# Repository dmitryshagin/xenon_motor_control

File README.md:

# xenon_motor_control
Board to control xenon headlight position with conventional halogen control for VW Passat B5+ car.
Bolt-con connectors that fit: Pigtail 968813-9C 0-1452576-8
https://aliexpress.ru/item/4000353686621.html?spm=a2g0s.9042311.0.0.ddc433edCFKElc

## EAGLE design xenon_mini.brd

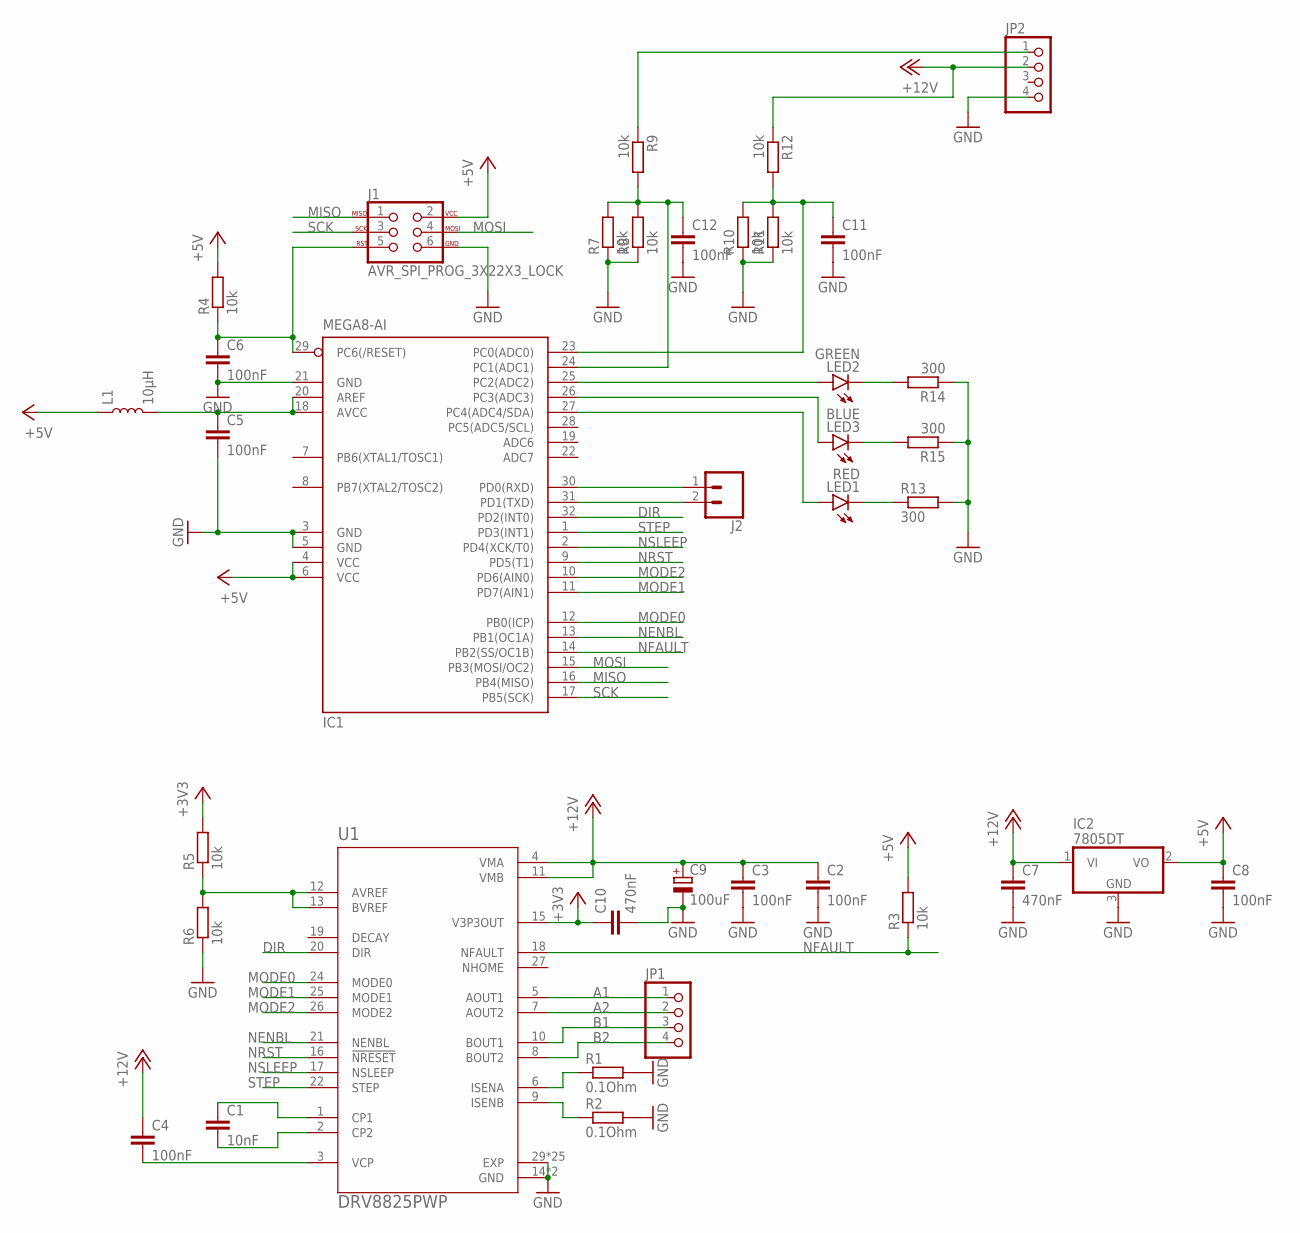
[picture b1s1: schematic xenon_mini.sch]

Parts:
C1: 10nF; C0603; LCSC C57112
C2, C3, C4, C8: 100nF; C0603; LCSC C14663
C5, C6, C11, C12: 100nF; C0603; LCSC CC0603KRX7R9BB104
C7, C10: 470nF; C0603; LCSC C1623
C9: 100uF; UD-6,3X7,7_NICHICON; LCSC C176675
IC1: MEGA8-AI; TQFP32-08; LCSC C8727
IC2: 7805DT; TO252; LCSC C310413
J1: AVR_SPI_PROG_3X22X3_LOCK; 2X3_LOCK
J2: CONN_02LOCK; 1X02_LOCK
JP1, JP2: PINHD-1X4; 1X04
L1: 10μH; 0805; LCSC C1046
LED1: RED; SML0603; LCSC C2286
LED2: GREEN; SML0603; LCSC C72043
LED3: BLUE; SML0603; LCSC C72041
R1, R2: 0.1Ohm; R1206; LCSC C25334
R3, R4, R5, R6, R7, R8, R9, R10, R11, R12: 10k; R0603; LCSC C25804
R13, R14, R15: 300; R0603; LCSC C23025
U1: DRV8825PWP; SOP65P640X120-29N; LCSC C81582

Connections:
+3V3: C10.1, R5.2, U1.15 (V3P3OUT)
+5V: C8.1, IC1.4 (VCC), IC1.6 (VCC), IC2.2 (VO), J1.2, L1.1, R3.2, R4.2
+12V: C2.1, C3.1, C4.1, C7.1, C9.+, IC2.1 (VI), JP2.2, R12.1, U1.4 (VMA), U1.11 (VMB)
A1: JP1.1, U1.5 (AOUT1)
A2: JP1.2, U1.7 (AOUT2)
B1: JP1.3, U1.10 (BOUT1)
B2: JP1.4, U1.8 (BOUT2)
DIR: IC1.32 (PD2(INT0)), U1.20 (DIR)
GND: C2.2, C3.2, C5.2, C6.2, C7.2, C8.2, C9.-, C10.2, C11.2, C12.2, IC1.3 (GND), IC1.5 (GND), IC1.21 (GND), IC2.3 (GND), J1.6, JP2.4, R1.2, R2.2, R6.1, R7.1, R8.1, R10.1, R11.1, R13.2, R14.1, R15.1, U1.14 (GND), U1.28 (GND), U1.29 (EXP), U1.P1 (EXP), U1.P2 (EXP), U1.P3 (EXP), U1.P4 (EXP), U1.P5 (EXP), U1.P6 (EXP), U1.P7 (EXP), U1.P8 (EXP), U1.P9 (EXP), U1.P10 (EXP), U1.P11 (EXP), U1.P12 (EXP), U1.P13 (EXP), U1.P14 (EXP), U1.P15 (EXP), U1.P16 (EXP), U1.P17 (EXP), U1.P18 (EXP), U1.P19 (EXP), U1.P20 (EXP), U1.P21 (EXP), U1.P22 (EXP), U1.P23 (EXP), U1.P24 (EXP)
MISO: IC1.16 (PB4(MISO)), J1.1
MODE0: IC1.12 (PB0(ICP)), U1.24 (MODE0)
MODE1: IC1.11 (PD7(AIN1)), U1.25 (MODE1)
MODE2: IC1.10 (PD6(AIN0)), U1.26 (MODE2)
MOSI: IC1.15 (PB3(MOSI/OC2)), J1.4
unnamed: C1.1, U1.1 (CP1)
unnamed: C1.2, U1.2 (CP2)
unnamed: C4.2, U1.3 (VCP)
unnamed: R1.1, U1.6 (ISENA)
unnamed: R2.1, U1.9 (ISENB)
unnamed: C6.1, IC1.29 (PC6(/RESET)), J1.5, R4.1
unnamed: C12.1, IC1.24 (PC1(ADC1)), R7.2, R8.2, R9.2
unnamed: C11.1, IC1.23 (PC0(ADC0)), R10.2, R11.2, R12.2
unnamed: LED1.C, R13.1
unnamed: JP2.1, R9.1
unnamed: R5.1, R6.2, U1.12 (AVREF), U1.13 (BVREF)
unnamed: IC1.30 (PD0(RXD)), J2.1
unnamed: IC1.31 (PD1(TXD)), J2.2
unnamed: IC1.25 (PC2(ADC2)), LED2.A
unnamed: IC1.26 (PC3(ADC3)), LED3.A
unnamed: LED2.C, R14.2
unnamed: LED3.C, R15.2
unnamed: IC1.27 (PC4(ADC4/SDA)), LED1.A
unnamed: C5.1, IC1.18 (AVCC), IC1.20 (AREF), L1.2
NENBL: IC1.13 (PB1(OC1A)), U1.21 (NENBL)
NFAULT: IC1.14 (PB2(SS/OC1B)), R3.1, U1.18 (NFAULT)
NRST: IC1.9 (PD5(T1)), U1.16 (!NRESET)
NSLEEP: IC1.2 (PD4(XCK/T0)), U1.17 (NSLEEP)
SCK: IC1.17 (PB5(SCK)), J1.3
STEP: IC1.1 (PD3(INT1)), U1.22 (STEP)

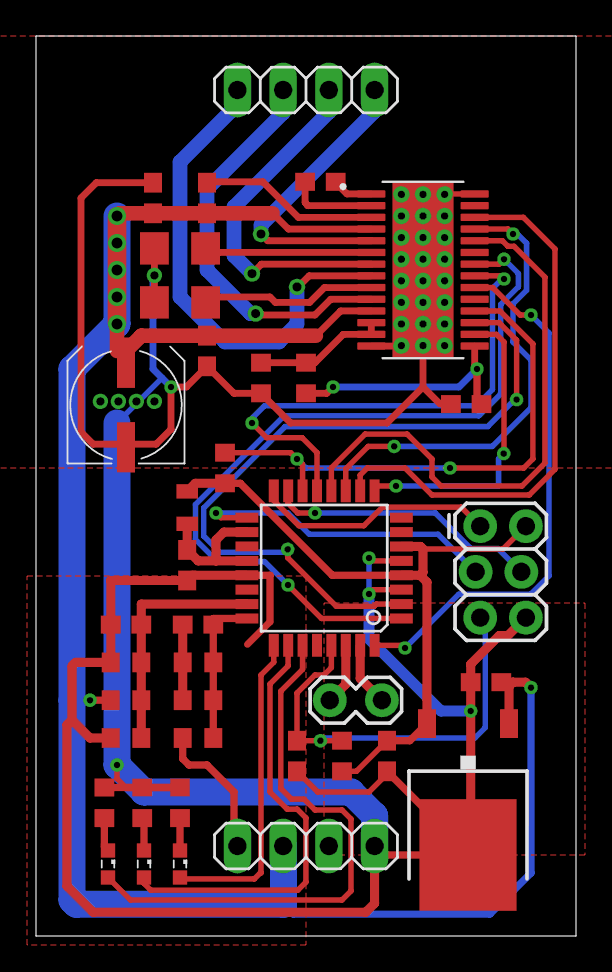
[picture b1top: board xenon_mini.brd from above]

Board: 2 copper layers, 30.0 x 50.0 mm, 38 parts (0 on the bottom side), 39 nets.

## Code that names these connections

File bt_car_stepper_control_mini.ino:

//+PC0 - voltage in
//+PC1 - corrector in

//+PC2 - green LED
//+PC3 - blue LED
//+PC4 - RED LED

//+PD2 - DIR 
//+PD3 - STEP
//+PD4 - NSLEEP
//+PD5 - NRST
//+PD6 - MODE1
//+PD7 - MODE2

//+PB0 - MODE0
//+PB1 - NENBL
//+PB2 - NFAULT
#define READS_TO_AVERAGE 50

const int dirPin = 2;
const int stepPin = 3;
const int sleepPin = 4;
const int resetPin = 5;
const int ms1Pin = 8;
const int ms2Pin = 7;
const int ms3Pin = 6;
const int enablePin = 9;
const int faultPin = 10;


const int voltageInPin = A0;
const int correctorInPin = A1;
const int greenLED = A2;
const int blueLED = A3;
const int redLED = A4;
const int step_delay = 600; //1000 is minimum for a full step
const int steps_total = 360; //its 360 full steps

int currentPosition = steps_total; //let's assume we are all way up un the start
uint32_t motor_last_moved_at = 0;

int previous_direction = 0;
uint8_t driver_enabled = 0;

uint32_t voltageIn = 0;
uint32_t correctorIn = 0;

uint32_t newVoltageIn = 0;
uint32_t newCorrectorIn = 0;
uint16_t reads_made = 0;
uint16_t reads_reference_made = 0;

int minVal = 0;
int maxVal = 1023;
int target = 0;

//for left headlight: GREEN - corrector input (pin 6), BLACK - +12 (pin2), RED - GND (pin 4)

// vin   = 13.4V
// corr0 = 11.1V . =>80% of vin => max
// corr1 = 9.7V
// corr2 = 7.7V
// corr3 = 5.4V <= 40% of vin => min.

void disable(){
//  digitalWrite(sleepPin, LOW);
  digitalWrite(enablePin, HIGH);
  digitalWrite(blueLED, LOW);
  driver_enabled = 0;
}

void enable(){
  if(driver_enabled){
    return;
  }
  digitalWrite(blueLED, HIGH);
  digitalWrite(enablePin, LOW);
//  delayMicroseconds(2000);
  delay(3);//it requires at least 1.7ms to start accepting data.
  driver_enabled = 1;
}

void moveToPosition(int target) {
  enable(); //power up driver
  int steps_count = 0;
  if(target < currentPosition) {
    digitalWrite(dirPin, LOW); // retract
    steps_count = currentPosition - target;
    previous_direction = 1;
  } else {
    digitalWrite(dirPin, HIGH); // extend
    steps_count = target - currentPosition;
    previous_direction = 0;
  }
  for (int x = 0; x < steps_count * 2; x++) { //x2 due to microstepping
    digitalWrite(stepPin, HIGH);
    delayMicroseconds(step_delay);
    digitalWrite(stepPin, LOW);
    delayMicroseconds(step_delay);
  }
  currentPosition = target;
//  disable(); // Release motor to avoid overheating
}

void setup() {
  delayMicroseconds(10000);
  pinMode(redLED, OUTPUT);
  digitalWrite(redLED, LOW);
  pinMode(greenLED, OUTPUT);
  digitalWrite(greenLED, HIGH);
  pinMode(blueLED, OUTPUT);
  digitalWrite(blueLED, LOW);
  pinMode(stepPin, OUTPUT);
  pinMode(dirPin, OUTPUT);
  
  pinMode(ms1Pin, OUTPUT);
  pinMode(ms2Pin, OUTPUT);
  pinMode(ms3Pin, OUTPUT);
  pinMode(resetPin, OUTPUT);
  pinMode(enablePin, OUTPUT);
  pinMode(sleepPin, OUTPUT);

  pinMode(faultPin, INPUT);

  pinMode(correctorInPin, INPUT);
  pinMode(voltageInPin, INPUT);

  digitalWrite(ms1Pin, HIGH);
  digitalWrite(ms2Pin, LOW);
  digitalWrite(ms3Pin, LOW); // Step to 1/2 step
  digitalWrite(resetPin, HIGH);
  digitalWrite(sleepPin, HIGH);
  disable();
  digitalWrite(blueLED, LOW);

  analogReference(EXTERNAL);
  
  Serial.begin(19200);
  moveToPosition(0); //fully retract shaft on start (35.5mm min, 48mm max)*/
  delay(10);
  disable();
  delay(1000);

  voltageIn = 0;
  correctorIn = 0;
  for(int i = 0; i < READS_TO_AVERAGE; i++){
    voltageIn += analogRead(voltageInPin);
    correctorIn += analogRead(correctorInPin);
  }
  voltageIn = voltageIn / READS_TO_AVERAGE;
  correctorIn = correctorIn / READS_TO_AVERAGE;
  delay(500);
}

void loop() {
  uint32_t time_since_last_moved = (millis() - motor_last_moved_at);

  if(!driver_enabled && (time_since_last_moved > target)){ //dont measure while motor is moving and some time after (proportional to position, to avoid oscillations
    if(reads_made < READS_TO_AVERAGE){
      newCorrectorIn += analogRead(correctorInPin);
      newVoltageIn += analogRead(voltageInPin);
      reads_made++;
    }else{
      correctorIn = newCorrectorIn / READS_TO_AVERAGE;
      newCorrectorIn = 0;
      voltageIn = newVoltageIn / READS_TO_AVERAGE;
      newVoltageIn = 0;
      minVal = voltageIn * 0.4; //everything below 40% is 0
      maxVal = voltageIn * 0.8; //everything above 80% is 100

      Serial.print("Cin: ");
      Serial.print(correctorIn);
      Serial.print("    Vin: ");
      Serial.print(voltageIn);
      Serial.print("    MinVal: ");
      Serial.print(minVal);
      Serial.print("    MaxVal: ");
      Serial.print(maxVal);
      Serial.print("    Target (cst): ");
      Serial.print(target);
      target = constrain(correctorIn, minVal, maxVal); // limit value
      target = map(target, minVal, maxVal, 180, steps_total); // scale value to produce desired step number. Will omit useless lowest positions
      Serial.print("    Target (map): ");
      Serial.println(target);

      Serial.print("    Position: ");
      Serial.println(currentPosition);
      reads_made = 0;
    }
  }
  
  digitalWrite(redLED, !digitalRead(faultPin));

  int error = (target-currentPosition);

  if( ( error > 0 && //no denoise if no direction change
        (
          (target < currentPosition && previous_direction == 1) ||
          (target > currentPosition && previous_direction == 0)
        )
      ) ||
      ((abs(error) > 2u) && ( time_since_last_moved > 1500 )) || //denoise for small steps
      ((abs(error) > 25u) && (time_since_last_moved > 200)) //to avoid rapid direction changes
     ){
    
    digitalWrite(stepPin, LOW);//keep it low just in case
    /*enable(); //enable driver
    if(target < currentPosition) {
      digitalWrite(dirPin, LOW); // retract
      previous_direction = 1;
      currentPosition--;
    } else {
      digitalWrite(dirPin, HIGH); // extend
      previous_direction = 0;
      currentPosition++;
    }
    digitalWrite(stepPin, HIGH);
    delayMicroseconds(step_delay);
    digitalWrite(stepPin, LOW);
    delayMicroseconds(step_delay);

    digitalWrite(stepPin, HIGH); //2 times due to microstepping.
    delayMicroseconds(step_delay);
    digitalWrite(stepPin, LOW);
    delayMicroseconds(step_delay);*/
    delay(currentPosition*2); //if motors are at different positions - delays will be different and it will reduce oscillations
    moveToPosition(target);
    delay(10);
    disable(); // Release motor to avoid overheating
    motor_last_moved_at = millis();
    delay(target*2);
  }else{
//    if(driver_enabled && (time_since_last_moved > 100)){ //disable driver, but don't do it too often. Driver affects readings heavily! And they interfeir between two lamps
//      //Serial.println(currentPosition);
//      disable();
//      delay(50);
//    }
//    delay(1);
  }

  /*if(!driver_enabled){// don't adjust reference - it will not adrift father than regulation inputs, but causes plenty of issues
    if(reads_reference_made < READS_REFERENCE_AVERAGE){
      newVoltageIn += analogRead(voltageInPin);
      reads_reference_made++;
    }else{
      voltageIn = newVoltageIn / READS_REFERENCE_AVERAGE;
      newVoltageIn = 0;
      reads_reference_made = 0;
    }
  }*/

}

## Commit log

2020-12-15 Make movement more syncronous for two motors
2021-10-12 Making regulation limits smaller + less jitter

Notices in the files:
parts and their libraries:
SparkFun-Connectors: Licensing: Creative Commons ShareAlike 4.0 International - https://creativecommons.org/licenses/by-sa/4.0
